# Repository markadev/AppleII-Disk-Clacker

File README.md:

# Apple II Disk Clacker

This is a small circuit to generate fake disk-seeking noises for Apple II disk emulators using a
mechanical relay. It connects transparently between the Apple II and any disk emulator to detect
disk activity and make noises.

https://github.com/user-attachments/assets/748217c7-e036-4df3-93b7-2d29ec6acae3

This should work with:
 * BMOW Floppy Emu in 5.25" mode (tested)
 * BMOW Floppy Emu in 3.5" mode
 * Other floppy emulators in 5.25" or 3.5" mode

This project will not work with:
 * Smartport devices like FujiNet

This is currently only a DIY project and **it requires a high-voltage ATtiny programmer**. I use a XGecu T48 programmer
but any other compatible programmer can be used. If you're looking for a similar noise-maker that you can just purchase
directly then check out the [Big Mess o' Wires Noisy Disk Mechanical Sounder](https://shop.bigmessowires.com/products/noisy-disk).

# Building

The repo includes all source files for building your own clacker or modifying the design:
 * [KiCad project for the hardware](./AppleII-Disk-Clacker)
 * [Arduino source code](./Clacker)

All the generated outputs are also included in standard readable formats so you don't have to install
KiCad or the Arduino IDE if you don't want to:
 * [Schematic](./AppleII-Disk-Clacker/AppleII-Disk-Clacker.pdf) for circuit reference
 * [gerber files](./AppleII-Disk-Clacker/outputs) for PCB manufacturing
 * [Pre-compiled ATtiny code](./Clacker/Clacker.ino.hex) to flash into the ATtiny

### Parts List

Most of the components can be substituted freely but I included specific part numbers that I used for
reference. You don't have to order from Mouser but I also included their part numbers so you can reference
their datasheets to find substitutes. I also created a shared [Mouser Project](https://www.mouser.com/Tools/Project/Share?AccessID=db4092a81a)
that you can use to check part availability and add all the components from the table to your cart at once.

If you're located in the US then you could [order 3 PCBs from OSH Park](https://oshpark.com/shared_projects/GrWe0x9J) for a reasonable amount,
or any cheap PCB manufacturer that you're comfortable with can do it.

| Reference | Qty | Value             | Mfr                  | MfrPartNo        | MouserPartNo         |
|-----------|-----|-------------------|----------------------|------------------|----------------------|
|  C1       |  1  | 0.1µ              | Vishay               | A104K15X7RF5TAA  | 594-A104K15X7RF5TAA  |
|  D1       |  1  | 1N4007            | Diotec Semiconductor | 1N4007           | 637-1N4007           |
|  J1,J2    |  2  | 20 Pin header     | Amphenol             | T821120A1S100CEU | 649-T821120A1S100CEU |
|  K1       |  1  | Relay             | Amphenol             | AWHSH105D00G     | 523-AWHSH105D00G     |
|  Q1       |  1  | 2N3904            | Diotec Semiconductor | 2N3904           | 637-2N3904           |
|  R1       |  1  | 2.2k              | KOA Speer            | MF1/4LCT52R222J  | 660-MF1/4LCT52R222J  |
|  U1       |  1  | ATtiny13A-P       | Microchip            | ATTINY13A-PU     | 556-ATTINY13A-PU     |
|  U1       |  1  | DIP-8 Socket      | TE Connectivity      | 1-2199298-2      | 571-1-2199298-2      |
|           |  2  | 20 Pin IDC socket | Wurth Elektronik     | 61202023021      | 710-61202023021      |

In addition to these components, you will also need a short length of 20 conductor 1.27mm pitch ribbon cable for the cable between your disk
emulator and the clacker. This is easy enough to salvage from old PC ribbon cables.

### Assembling

Assembly is pretty straightforward since there are not many components. Just start by soldering the lowest profile components first
and ensure the orientation of components match the labeling on the PCB.

If you're also making a 20 pin ribbon cable then make sure that the same wire is entering the marked pin 1 position on both connector housings.
The ribbon cable can enter either side of the housing as long as that wire lines up with the pin 1 position. This lets you construct a
cable with the polarization nub in the orientation that is the most convientent for your disk emulator.

### Flashing the ATtiny

These steps will vary depending on the programmer and software you use. A high-voltage ATtiny programmer is required. I can confirm that the
XGecu T48 programmer works but I am sure there are many others.

1. Select the ATtiny13a device (DIP8 packaging if the different packages are listed) in your programming software.
2. Load [the .hex file](./Clacker/Clacker.ino.hex) into your programming software. Make sure to load it as a hex file and not as a binary file.
3. Find and open the tab or dialog box to set the ATtiny fuse values. In the Xgpro application these settings are on the "Config" tab.
   * set CKDIV8 = 0  (divides clock by 8; this is the default fuse value for an ATtiny13)
   * set CKSEL1:0 = 10  (uses internal 9.6MHz oscillator; these are the default fuse values for an ATtiny13)
   * enable RSTDISBL  (disables /RESET so it can be used as GPIO)
4. Program the ATtiny

# Using

To use the clacker, just connect one of the 20 pin connectors to your disk emulator (like the Big Mess o' Wires Floppy Emu or a similar device)
and connect the other end to your disk controller card. It doesn't matter which cable goes to which connector, just make sure that pin 1 on the
cable connects to pin 1 on the connector.

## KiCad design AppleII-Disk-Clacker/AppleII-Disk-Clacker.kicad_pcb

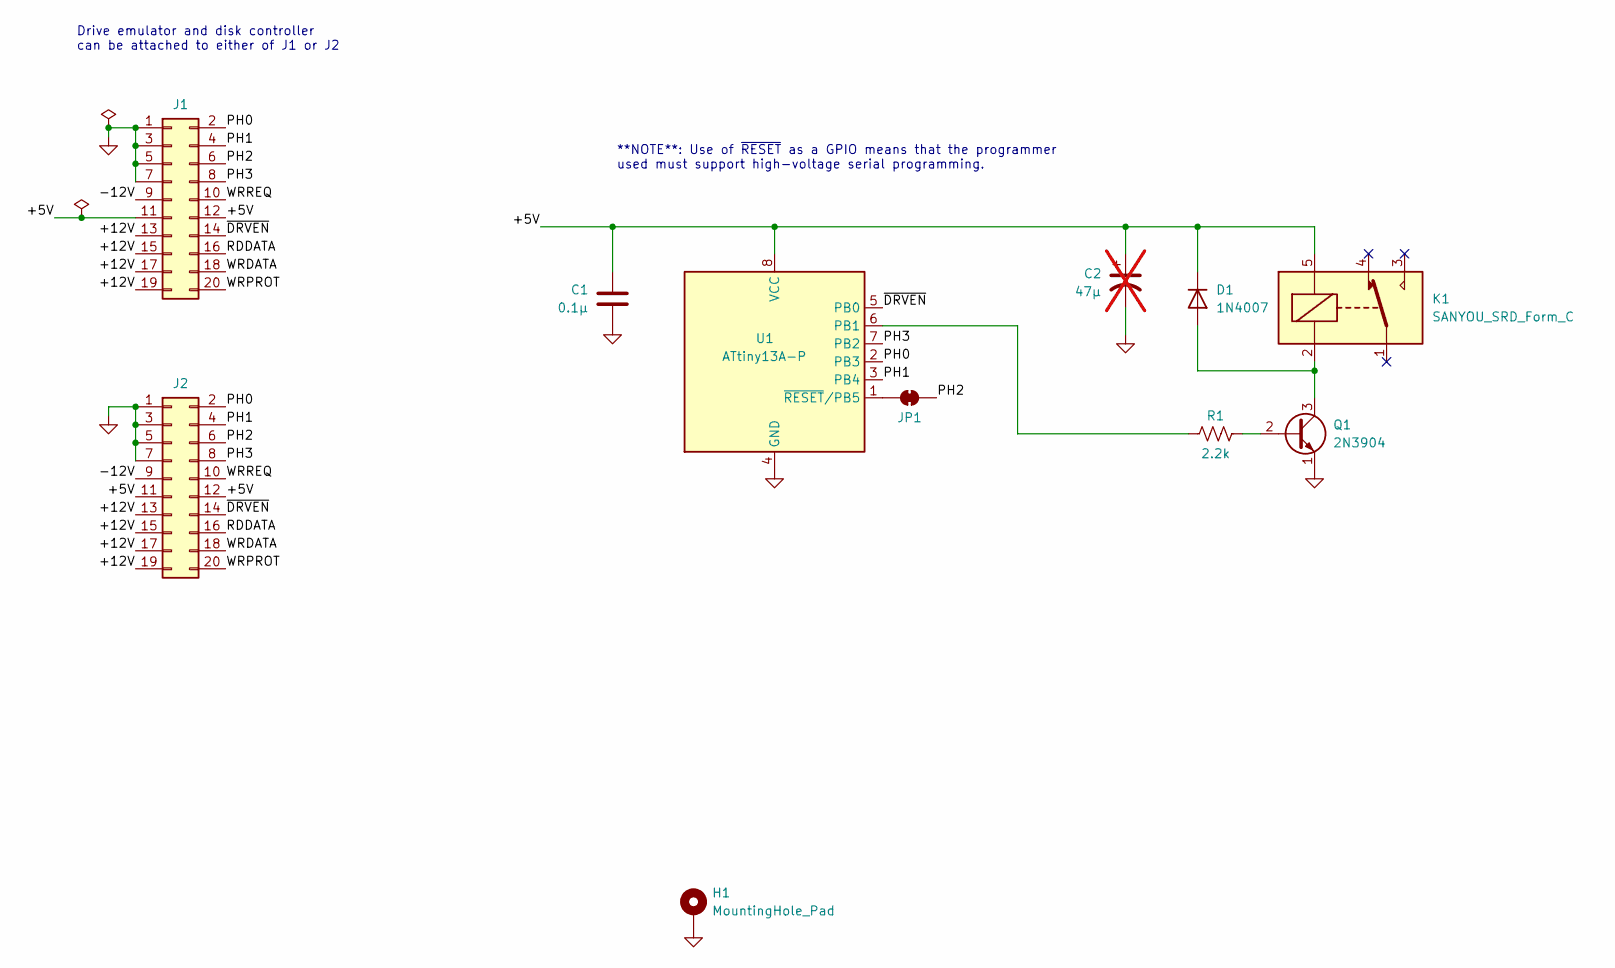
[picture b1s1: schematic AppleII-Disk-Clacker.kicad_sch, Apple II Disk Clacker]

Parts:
C1: 0.1µ; C_Axial_L3.8mm_D2.6mm_P10.00mm_Horizontal; MfrPartNo A104K15X7RF5TAA; MouserPartNo 594-A104K15X7RF5TAA
C2: 47µ; CP_Radial_D6.3mm_P2.50mm; MfrPartNo ECE-A1EKA470B; MouserPartNo 667-ECE-A1EKA470B; not fitted
D1: 1N4007; D_DO-41_SOD81_P10.16mm_Horizontal; MfrPartNo 1N4007; MouserPartNo 637-1N4007
H1: MountingHole_Pad; MountingHole_3.2mm_M3_Pad
J1, J2: Conn_02x10_Odd_Even; IDC-Header_2x10_P2.54mm_Vertical; MfrPartNo T821120A1S100CEU; MouserPartNo 649-T821120A1S100CEU
JP1: SolderJumper_2_Bridged; SolderJumper-2_P1.3mm_Bridged_RoundedPad1.0x1.5mm
K1: SANYOU_SRD_Form_C; Relay_SPDT_SANYOU_SRD_Series_Form_C; MfrPartNo AWHSH105D00G; MouserPartNo 523-AWHSH105D00G
Q1: 2N3904; TO-92_Inline_Wide; MfrPartNo 2N3904; MouserPartNo 637-2N3904
R1: 2.2k; R_Axial_DIN0309_L9.0mm_D3.2mm_P12.70mm_Horizontal; MfrPartNo MF1/4LCT52R222J; MouserPartNo 660-MF1/4LCT52R222J
U1: ATtiny13A-P; DIP-8_W7.62mm_Socket; MfrPartNo ATTINY13A-PU; MouserPartNo 556-ATTINY13A-PU

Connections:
/+5V: C1.1, C2.1, D1.1 (K), J1.11, J1.12, J2.11, J2.12, K1.5, U1.8 (VCC)
/+12V: J1.13, J1.15, J1.17, J1.19, J2.13, J2.15, J2.17, J2.19
/-12V: J1.9, J2.9
/PH0: J1.2, J2.2, U1.2 (PB3)
/PH1: J1.4, J2.4, U1.3 (PB4)
/PH2: J1.6, J2.6, JP1.2 (B)
/PH3: J1.8, J2.8, U1.7 (PB2)
/RDDATA: J1.16, J2.16
/WRDATA: J1.18, J2.18
/WRPROT: J1.20, J2.20
/WRREQ: J1.10, J2.10
/~DRVEN: J1.14, J2.14, U1.5 (PB0)
GND: C1.2, C2.2, H1.1, J1.1, J1.3, J1.5, J1.7, J2.1, J2.3, J2.5, J2.7, Q1.1 (E), U1.4 (GND)
unnamed: D1.2 (A), K1.2, Q1.3 (C)
unnamed: JP1.1 (A), U1.1 (~RESET/PB5)
unnamed: Q1.2 (B), R1.2
unnamed: R1.1, U1.6 (PB1)

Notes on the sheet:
**NOTE**: Use of ~{RESET} as a GPIO means that the programmer used must support high-voltage serial programming.
Drive emulator and disk controller can be attached to either of J1 or J2

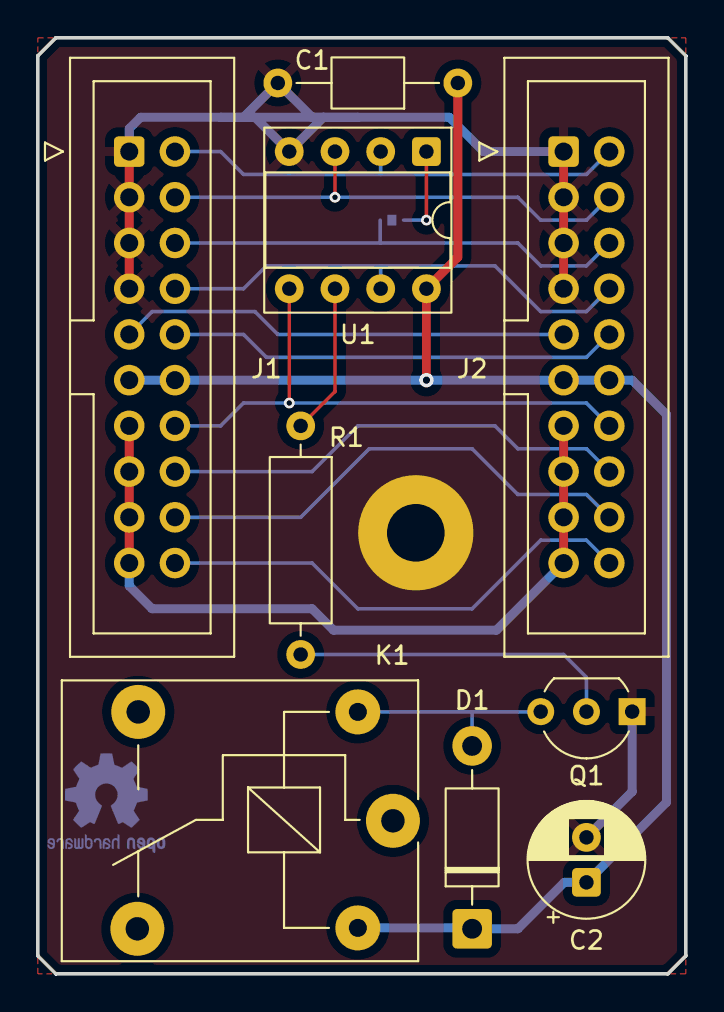
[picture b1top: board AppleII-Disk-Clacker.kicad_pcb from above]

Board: 2 copper layers, 36.0 x 52.0 mm, 11 parts (1 on the bottom side), 17 nets.

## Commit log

2025-09-27 Initial checkin
2025-09-27 Add a README
2025-09-27 Add video to README
2025-09-27 Add OSH Park link

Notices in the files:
AppleII-Disk-Clacker/AppleII-Disk-Clacker.kicad_pcb:
Licensed under CERN-OHL-P V2.0 (https://ohwr.org/cern_ohl_p_v2.txt)
Copyright (C) 2025 Mark Aikens
